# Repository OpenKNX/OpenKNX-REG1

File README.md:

# OpenKNX-REG1

see Wiki: https://github.com/OpenKNX/OpenKNX/wiki/OpenKNX-REG1

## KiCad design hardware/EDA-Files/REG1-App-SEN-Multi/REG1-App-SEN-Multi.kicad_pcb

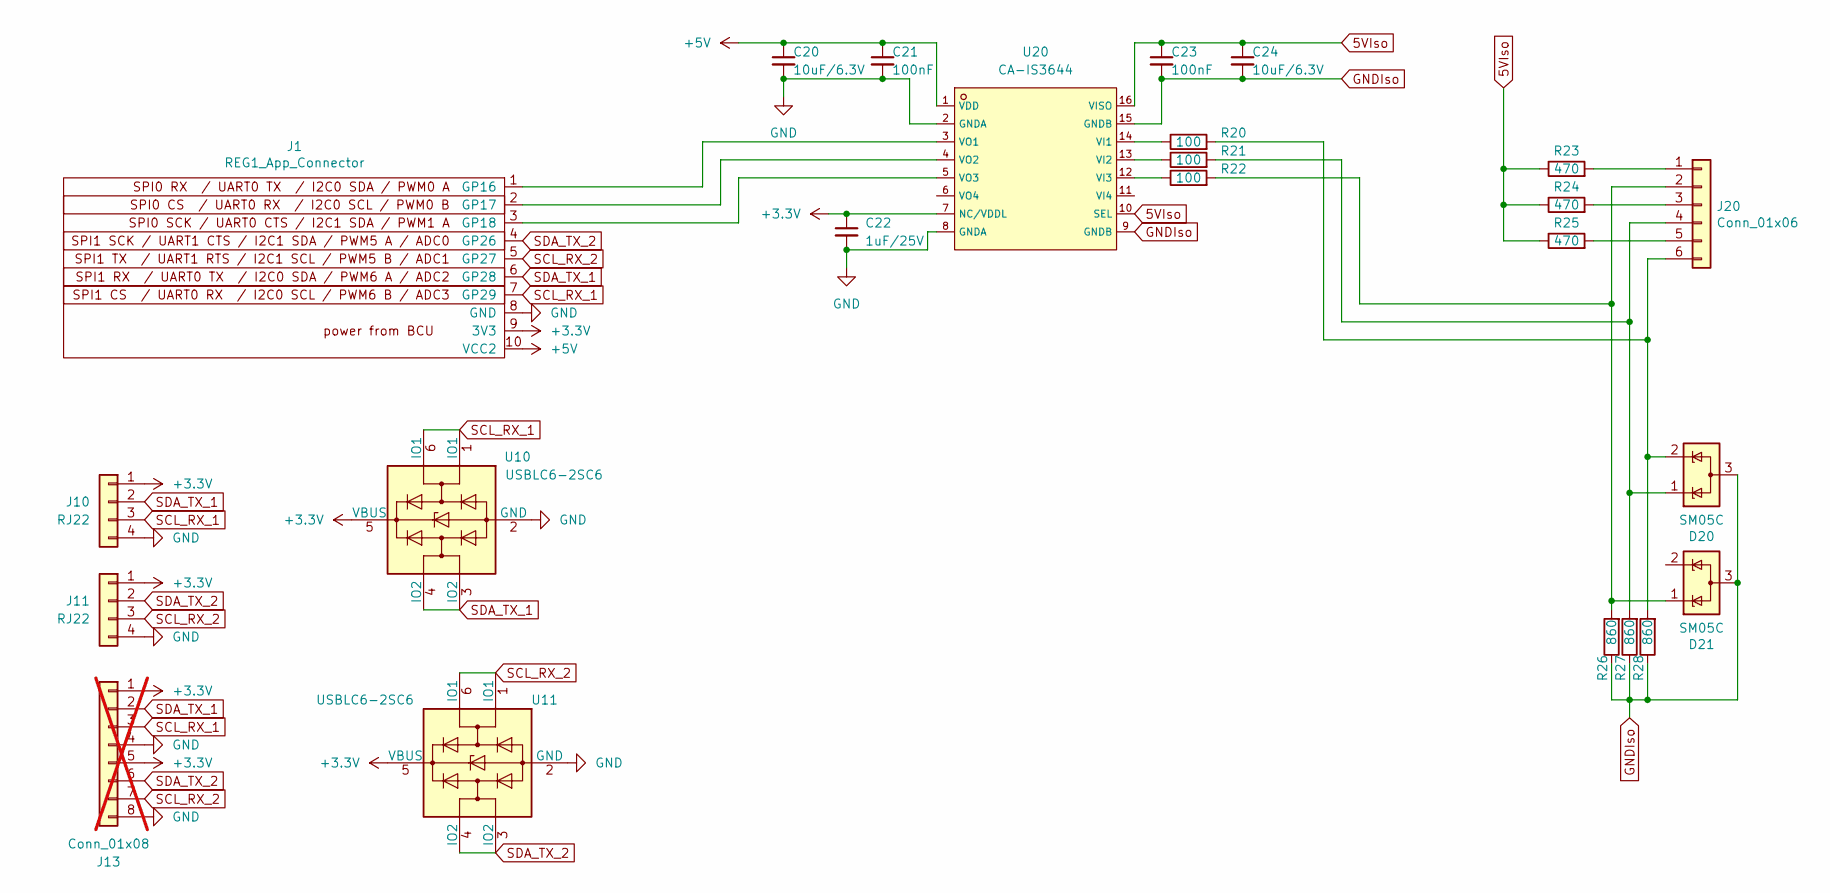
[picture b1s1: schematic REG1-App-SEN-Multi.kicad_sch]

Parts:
C20, C24: 10uF/6.3V; C_0402_1005Metric
C21, C23: 100nF; C_0402_1005Metric
C22: 1uF/25V; C_0402_1005Metric
D20, D21: SM05C; SOT-23
J1: REG1_App_Connector; PinHeader_1x10_P2.54mm_Horizontal
J10, J11: RJ22
J13: Conn_01x08; CONN-TH_8P-P2.54_DIBO_DB2ERC-2.54-8P-GN; not fitted
J20: Conn_01x06; PhoenixContact_MC_1,5_6-G-3.5_1x06_P3.50mm_Horizontal
R20, R21, R22: 100; R_0603_1608Metric
R23, R24, R25: 470; R_0603_1608Metric
R26, R27, R28: 860; R_0603_1608Metric
U10, U11: USBLC6-2SC6; SOT-23-6
U20: CA-IS3644; WSOIC-16_L10.3-W7.5-P1.27-LS10.3-BL

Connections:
5VIso: C23.1, C24.1, R23.1, R24.1, R25.1, U20.10 (SEL), U20.16 (VISO)
+3.3V: C22.1, J1.9 (3V3), J10.1, J11.1, J13.1, J13.5, U10.5 (VBUS), U11.5 (VBUS), U20.7 (NC/VDDL)
+5V: C20.1, C21.1, J1.10 (VCC2), U20.1 (VDD)
GND: C20.2, C21.2, C22.2, J1.8 (GND), J10.4, J11.4, J13.4, J13.8, U10.2 (GND), U11.2 (GND), U20.2 (GNDA), U20.8 (GNDA)
GNDIso: C23.2, C24.2, D20.3 (A), D21.3 (A), R26.1, R27.1, R28.1, U20.9 (GNDB), U20.15 (GNDB)
unnamed: J1.1 (GP16), U20.3 (VO1)
unnamed: J1.2 (GP17), U20.4 (VO2)
unnamed: J1.3 (GP18), U20.5 (VO3)
unnamed: J20.1, R23.2
unnamed: D21.1 (K), J20.2, R22.2, R26.2
unnamed: J20.3, R24.2
unnamed: D20.1 (K), J20.4, R21.2, R27.2
unnamed: J20.5, R25.2
unnamed: D20.2 (K), J20.6, R20.2, R28.2
unnamed: R20.1, U20.14 (VI1)
unnamed: R21.1, U20.13 (VI2)
unnamed: R22.1, U20.12 (VI3)
SCL_RX_1: J1.7 (GP29), J10.3, J13.3, U10.1 (IO1), U10.6 (IO1)
SCL_RX_2: J1.5 (GP27), J11.3, J13.7, U11.1 (IO1), U11.6 (IO1)
SDA_TX_1: J1.6 (GP28), J10.2, J13.2, U10.3 (IO2), U10.4 (IO2)
SDA_TX_2: J1.4 (GP26), J11.2, J13.6, U11.3 (IO2), U11.4 (IO2)

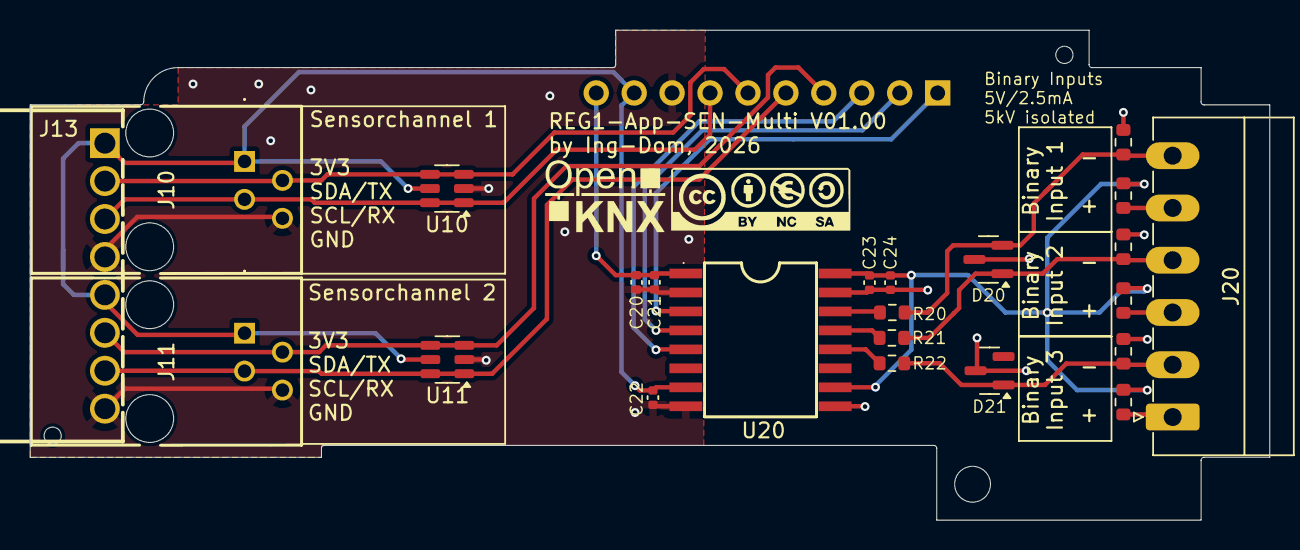
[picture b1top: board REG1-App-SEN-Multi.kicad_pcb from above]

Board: 2 copper layers, 83.0 x 32.8 mm, 24 parts (1 on the bottom side), 21 nets.

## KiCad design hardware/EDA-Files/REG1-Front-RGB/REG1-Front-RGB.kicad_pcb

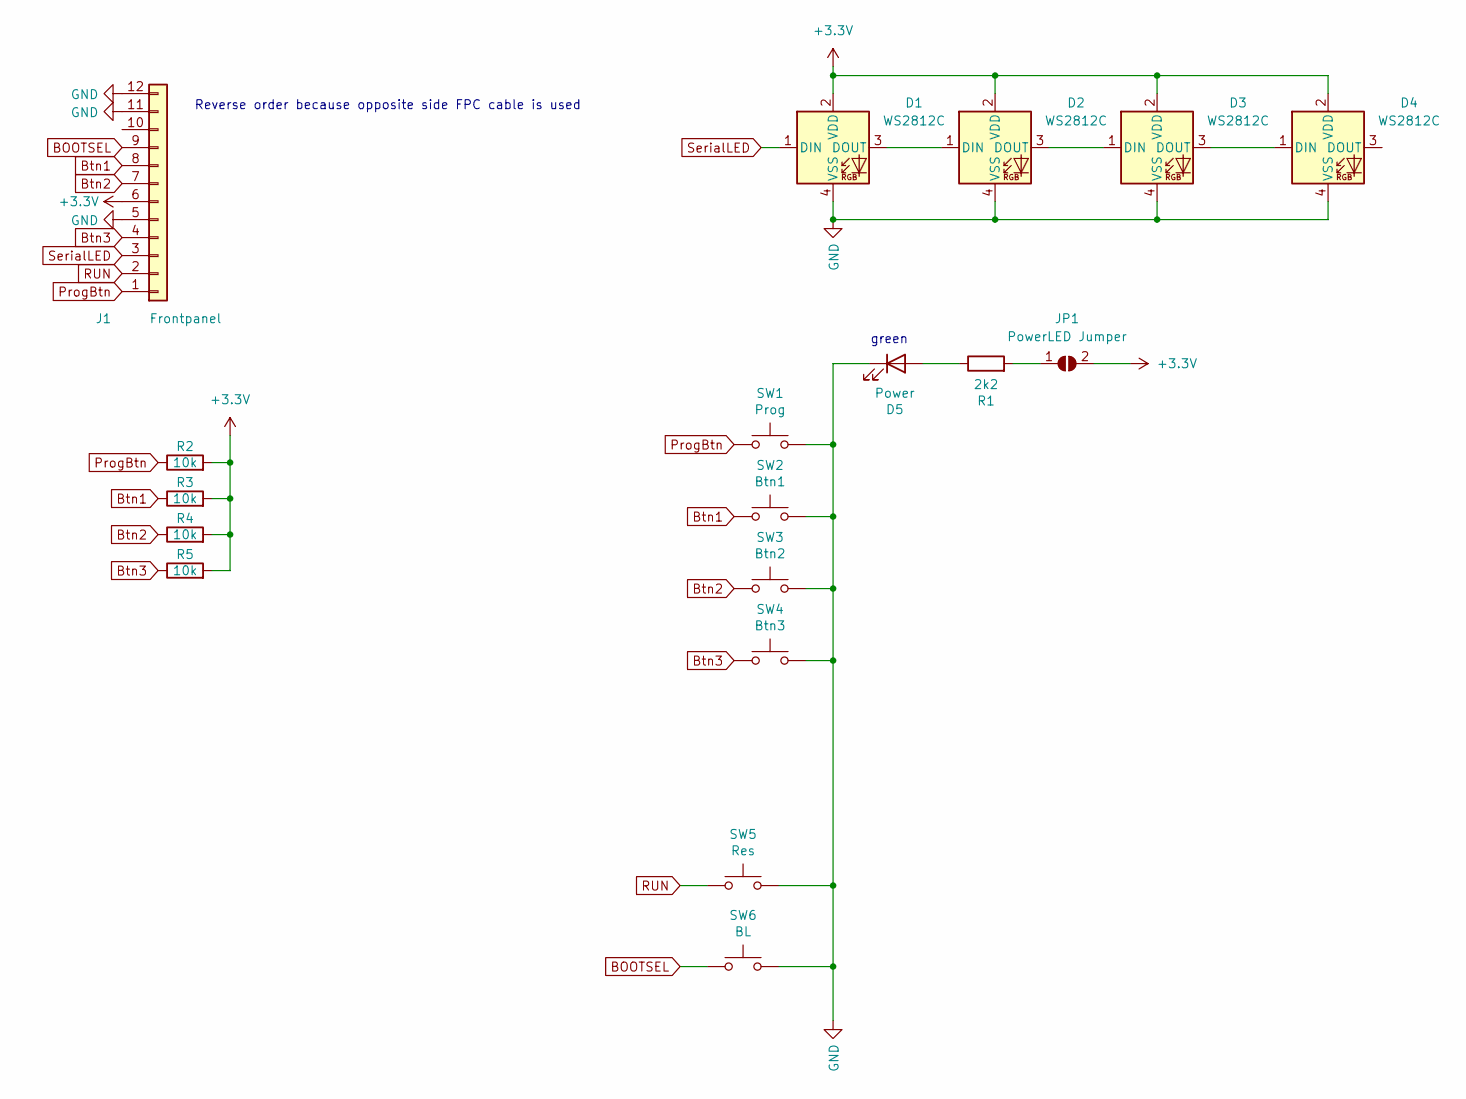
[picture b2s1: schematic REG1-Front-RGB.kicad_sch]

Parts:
D1, D2, D3, D4: WS2812C; LED-SMD_4P-L2.7-W2.4-TL_WS2812C-2427_Handsolder
D5: Power; LED_0603_1608Metric
J1: Frontpanel; C11050_FPC-SMD_P0.5-10P_LSXJ-H2.0-10P
JP1: PowerLED Jumper; SolderJumper-2_P1.3mm_Open_RoundedPad1.0x1.5mm
R1: 2k2; R_0402_1005Metric
R2, R3, R4, R5: 10k; R_0402_1005Metric
SW1: Prog; C455282_SW-SMD_4P-L4.2-W3.3-P2.15-LS5.1
SW2: Btn1; C455282_SW-SMD_4P-L4.2-W3.3-P2.15-LS5.1
SW3: Btn2; C455282_SW-SMD_4P-L4.2-W3.3-P2.15-LS5.1
SW4: Btn3; C455282_SW-SMD_4P-L4.2-W3.3-P2.15-LS5.1
SW5: Res; C455282_SW-SMD_4P-L4.2-W3.3-P2.15-LS5.1
SW6: BL; C455282_SW-SMD_4P-L4.2-W3.3-P2.15-LS5.1

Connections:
+3.3V: D1.2 (VDD), D2.2 (VDD), D3.2 (VDD), D4.2 (VDD), J1.6, JP1.2 (B), R2.2, R3.2, R4.2, R5.2
BOOTSEL: J1.9, SW6.1
Btn1: J1.8, R3.1, SW2.1
Btn2: J1.7, R4.1, SW3.1
Btn3: J1.4, R5.1, SW4.1
GND: D1.4 (VSS), D2.4 (VSS), D3.4 (VSS), D4.4 (VSS), D5.1 (K), J1.5, J1.11, J1.12, SW1.2, SW2.2, SW3.2, SW4.2, SW5.2, SW6.2
unnamed: D1.3 (DOUT), D2.1 (DIN)
unnamed: D2.3 (DOUT), D3.1 (DIN)
unnamed: D3.3 (DOUT), D4.1 (DIN)
unnamed: D5.2 (A), R1.1
unnamed: JP1.1 (A), R1.2
ProgBtn: J1.1, R2.1, SW1.1
RUN: J1.2, SW5.1
SerialLED: D1.1 (DIN), J1.3

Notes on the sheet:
green
Reverse order because opposite side FPC cable is used

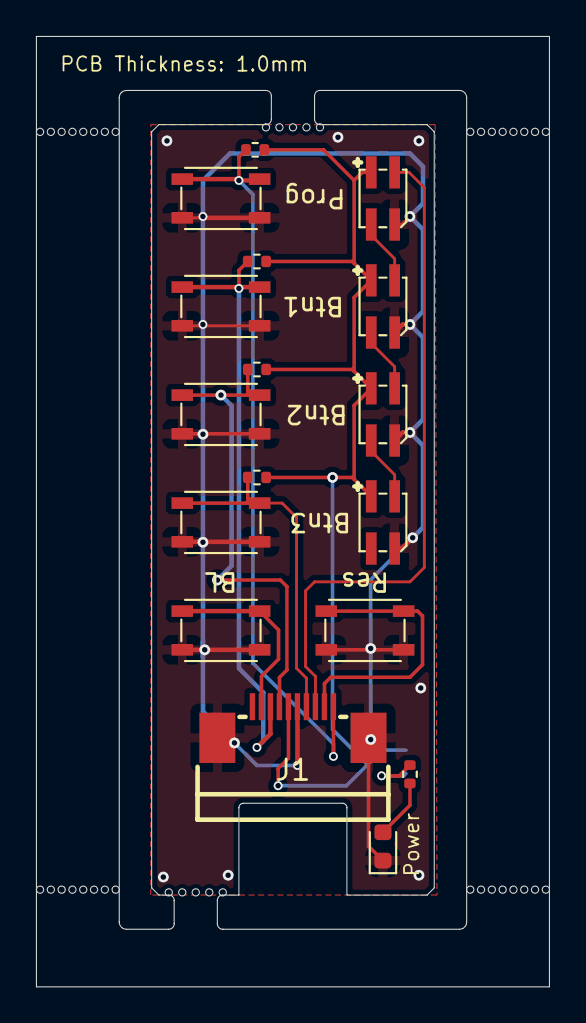
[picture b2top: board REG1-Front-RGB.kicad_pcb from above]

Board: 2 copper layers, 28.5 x 52.8 mm, 24 parts (1 on the bottom side), 14 nets.

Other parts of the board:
e: VAL**; mouse-bite-5.00mm-frame
e#2: VAL**; mouse-bite-5.00mm-frame
mouse-bite: mouse-bite-2.00mm-slot_1side
mouse-bite#2, mouse-bite#3: VAL**; mouse-bite-5.00mm-frame
mouse-bite#4: mouse-bite-2.00mm-slot_1side

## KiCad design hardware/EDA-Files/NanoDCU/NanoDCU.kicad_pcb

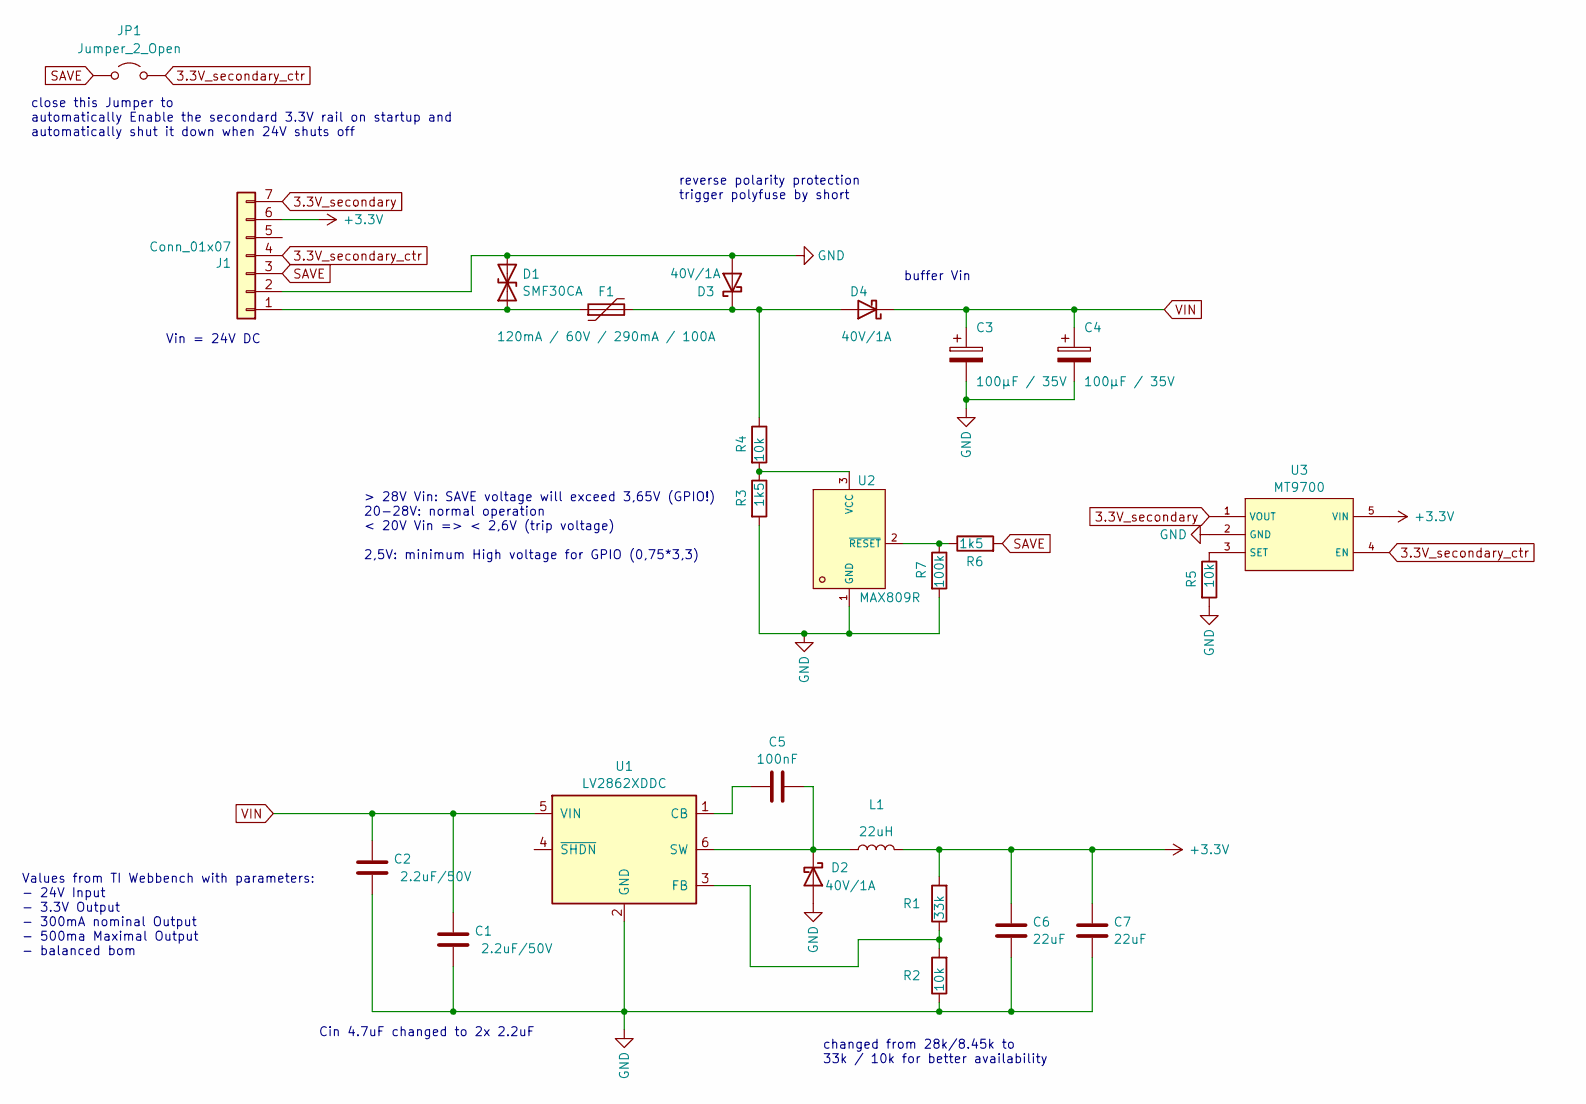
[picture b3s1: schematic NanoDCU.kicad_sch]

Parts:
C1, C2: 2.2uF/50V; C_0805_2012Metric
C3, C4: 100µF / 35V; CP_Elec_6.3x5.8
C5: 100nF; C_0402_1005Metric
C6, C7: 22uF; C_0805_2012Metric
D1: SMF30CA; D_SOD-123F
D2, D3, D4: 40V/1A; D_SOD-123
F1: 120mA / 60V / 290mA / 100A; Fuse_1206_3216Metric
J1: Conn_01x07; PinHeader_1x07_P2.54mm_Vertical
JP1: Jumper_2_Open; SolderJumper-2_P1.3mm_Open_RoundedPad1.0x1.5mm
L1: 22uH; L_Sunlord_SWPA4020
R1: 33k; R_0402_1005Metric
R2, R4, R5: 10k; R_0402_1005Metric
R3, R6: 1k5; R_0402_1005Metric
R7: 100k; R_0402_1005Metric
U1: LV2862XDDC; SOT-23-6
U2: MAX809R; SOT-23
U3: MT9700; SOT-23-5

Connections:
3.3V_secondary: J1.7, U3.1 (VOUT)
3.3V_secondary_ctr: J1.4, JP1.2 (B), U3.4 (EN)
+3.3V: C6.1, C7.1, J1.6, L1.2, R1.2, U3.5 (VIN)
GND: C1.2, C2.2, C3.2, C4.2, C6.2, C7.2, D1.2 (A2), D2.2 (A), D3.2 (A), J1.2, R2.1, R3.2, R5.2, R7.2, U1.2 (GND), U2.1 (GND), U3.2 (GND)
unnamed: D1.1 (A1), F1.1, J1.1
unnamed: C5.2, D2.1 (K), L1.1, U1.6 (SW)
unnamed: D3.1 (K), D4.2 (A), F1.2, R4.1
unnamed: C5.1, U1.1 (CB)
unnamed: R1.1, R2.2, U1.3 (FB)
unnamed: R3.1, R4.2, U2.3 (VCC)
unnamed: R6.1, R7.1, U2.2 (~RESET)
unnamed: R5.1, U3.3 (SET)
SAVE: J1.3, JP1.1 (A), R6.2
VIN: C1.1, C2.1, C3.1, C4.1, D4.1 (K), U1.5 (VIN)

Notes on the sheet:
> 28V Vin: SAVE voltage will exceed 3,65V (GPIO!) 20-28V: normal operation < 20V Vin => < 2,6V (trip voltage) 2,5V: minimum High voltage for GPIO (0,75*3,3)
changed from 28k/8.45k to 33k / 10k for better availability
reverse polarity protection trigger polyfuse by short
close this Jumper to automatically Enable the secondard 3.3V rail on startup and automatically shut it down when 24V shuts off
Cin 4.7uF changed to 2x 2.2uF
Vin = 24V DC
buffer Vin
Values from TI Webbench with parameters: - 24V Input - 3.3V Output - 300mA nominal Output - 500ma Maximal Output - balanced bom

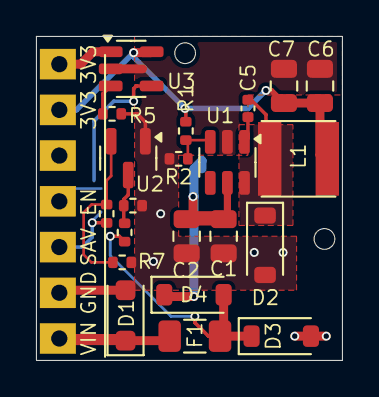
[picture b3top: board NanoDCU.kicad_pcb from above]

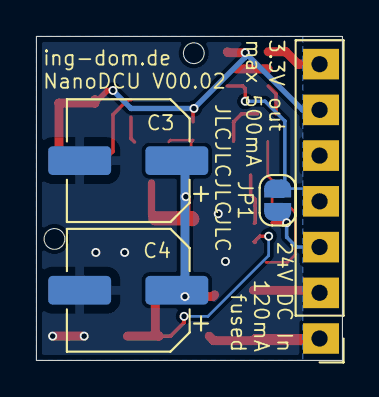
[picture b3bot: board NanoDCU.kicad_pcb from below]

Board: 2 copper layers, 17.0 x 18.0 mm, 25 parts (4 on the bottom side), 14 nets.

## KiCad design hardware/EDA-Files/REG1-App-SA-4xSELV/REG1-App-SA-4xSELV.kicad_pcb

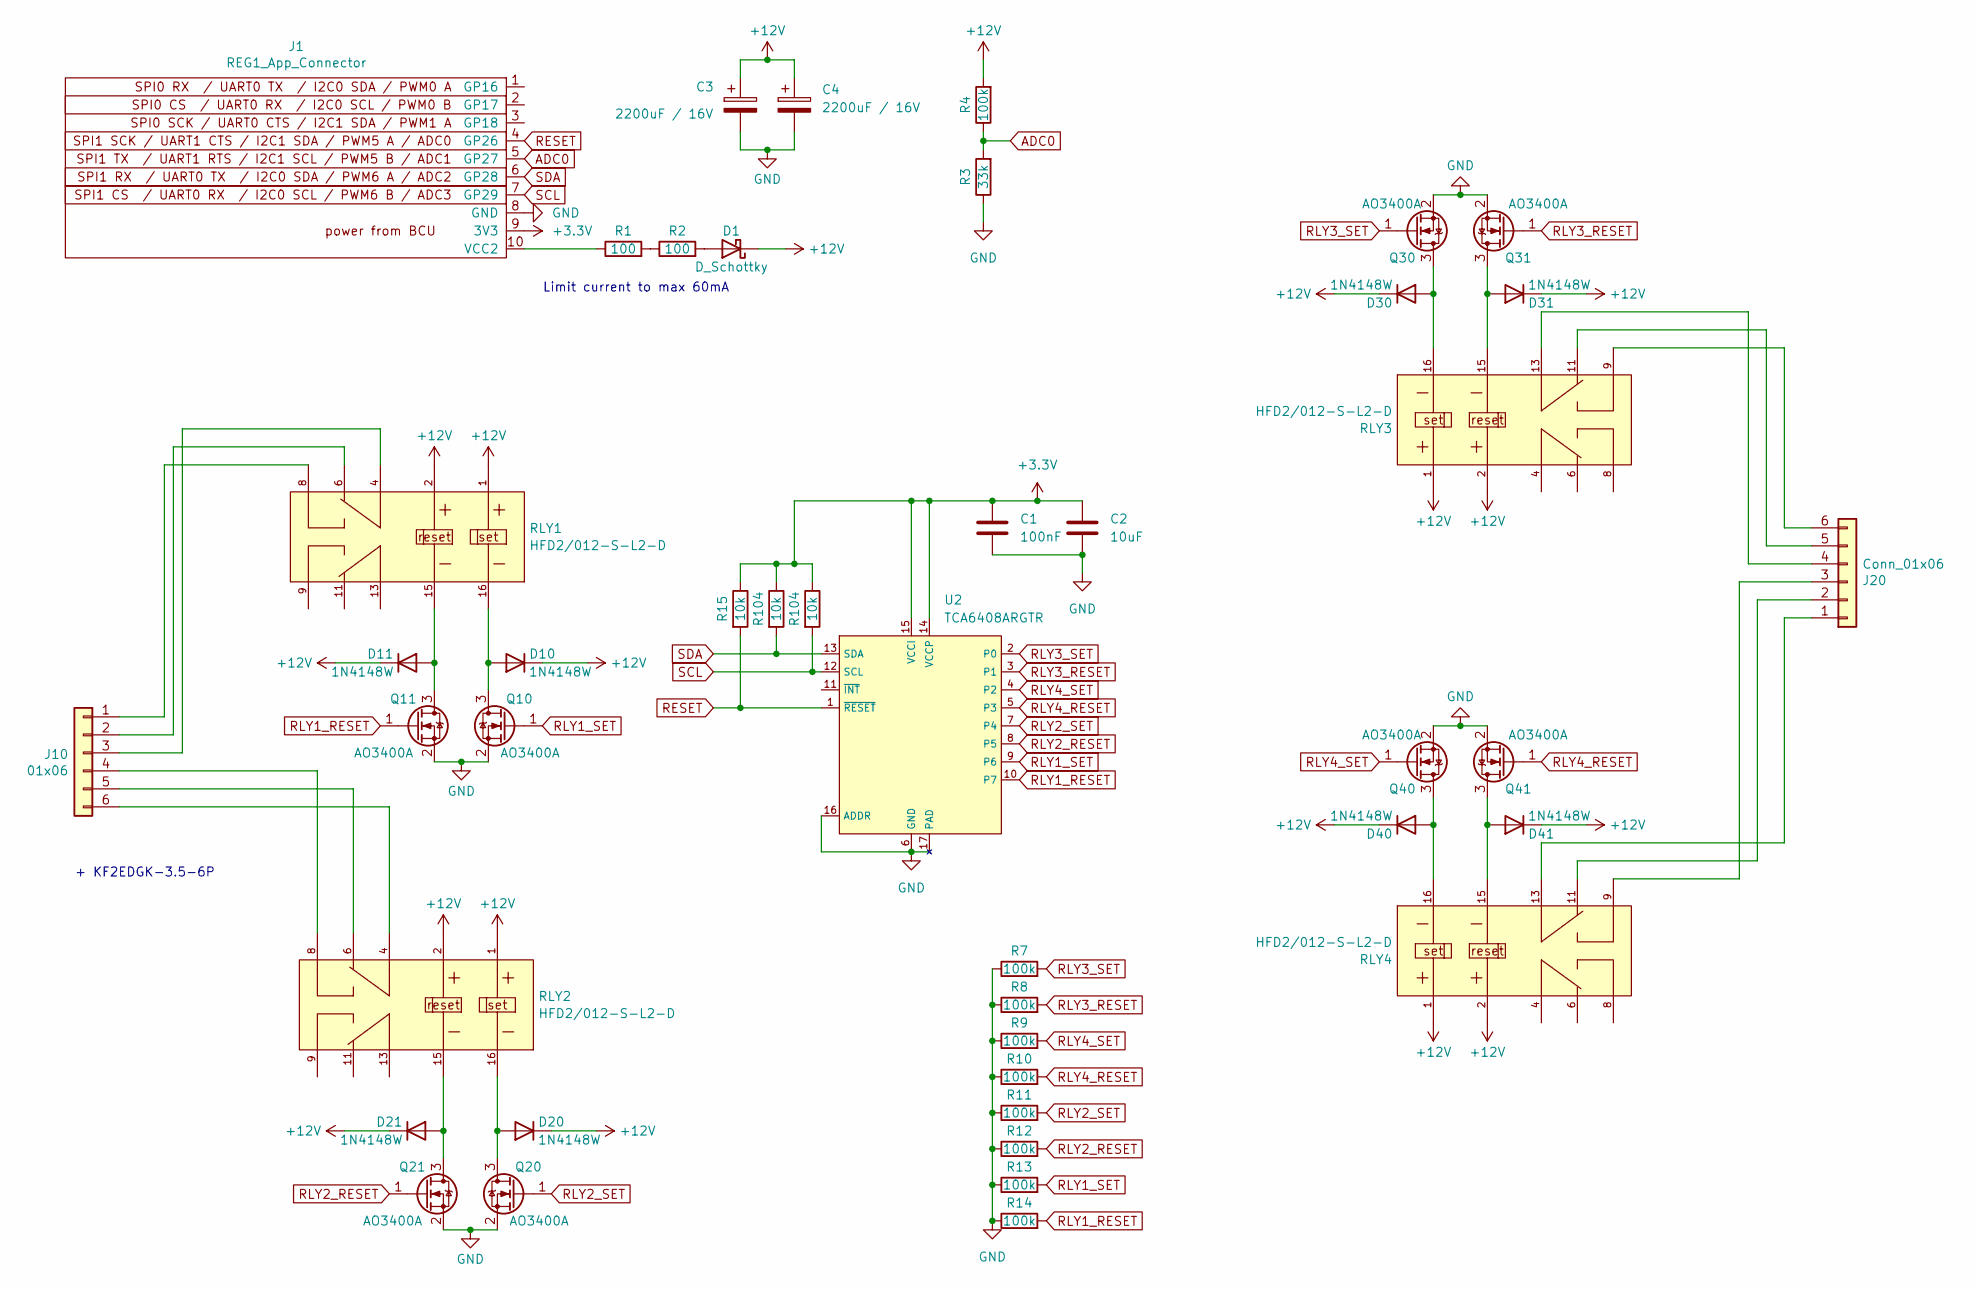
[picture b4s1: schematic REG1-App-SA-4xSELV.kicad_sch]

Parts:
C1: 100nF; R_0402_1005Metric
C2: 10uF; R_0805_2012Metric
C3, C4: 2200uF / 16V; CP_Radial_D10.0mm_H20.0mm_P5.00mm_Horizontal
D1: D_Schottky; D_SOD-323
D10, D11, D20, D21, D30, D31, D40, D41: 1N4148W; D_SOD-323
J1: REG1_App_Connector; PinHeader_1x10_P2.54mm_Horizontal
J10: 01x06; PhoenixContact_MC_1,5_6-G-3.5_1x06_P3.50mm_Horizontal
J20: Conn_01x06; PhoenixContact_MC_1,5_6-G-3.5_1x06_P3.50mm_Horizontal
Q10, Q11, Q20, Q21, Q30, Q31, Q40, Q41: AO3400A; SOT-23
R1, R2: 100; R_1206_3216Metric
R3: 33k; R_0402_1005Metric
R4, R7, R8, R9, R10, R11, R12, R13, R14: 100k; R_0402_1005Metric
R15, R104: 10k; R_0402_1005Metric
RLY1, RLY2, RLY3, RLY4: HFD2/012-S-L2-D; RELAY-TH_HFD2-X-X-L2-X
U2: TCA6408ARGTR; QFN-16-1EP_3x3mm_P0.5mm_EP1.7x1.7mm

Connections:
+3.3V: C1.1, C2.1, J1.9 (3V3), R15.1, U2.14 (VCCP), U2.15 (VCCI); also elsewhere on the board
+12V: C3.1, C4.1, D1.1 (K), D10.1 (K), D11.1 (K), D20.1 (K), D21.1 (K), D30.1 (K), D31.1 (K), D40.1 (K), D41.1 (K), R4.2, RLY1.1, RLY1.2, RLY2.1, RLY2.2, RLY3.1, RLY3.2, RLY4.1, RLY4.2
ADC0: J1.5 (GP27), R3.2, R4.1
GND: C1.2, C2.2, C3.2, C4.2, J1.8 (GND), Q10.2 (S), Q11.2 (S), Q20.2 (S), Q21.2 (S), Q30.2 (S), Q31.2 (S), Q40.2 (S), Q41.2 (S), R3.1, R7.1, R8.1, R9.1, R10.1, R11.1, R12.1, R13.1, R14.1, U2.6 (GND), U2.16 (ADDR), U2.17 (PAD)
unnamed: D1.2 (A), R2.2
unnamed: D10.2 (A), Q10.3 (D), RLY1.16
unnamed: D11.2 (A), Q11.3 (D), RLY1.15
unnamed: D20.2 (A), Q20.3 (D), RLY2.16
unnamed: D21.2 (A), Q21.3 (D), RLY2.15
unnamed: D30.2 (A), Q30.3 (D), RLY3.16
unnamed: D31.2 (A), Q31.3 (D), RLY3.15
unnamed: D40.2 (A), Q40.3 (D), RLY4.16
unnamed: D41.2 (A), Q41.3 (D), RLY4.15
unnamed: J1.10 (VCC2), R1.1
unnamed: J10.1, RLY1.8
unnamed: J10.2, RLY1.6
unnamed: J10.3, RLY1.4
unnamed: J10.4, RLY2.8
unnamed: J10.5, RLY2.6
unnamed: J10.6, RLY2.4
unnamed: J20.1, RLY4.13
unnamed: J20.2, RLY4.11
unnamed: J20.3, RLY4.9
unnamed: J20.4, RLY3.13
unnamed: J20.5, RLY3.11
unnamed: J20.6, RLY3.9
unnamed: R1.2, R2.1
RESET: J1.4 (GP26), R15.2, U2.1 (~RESET)
RLY1_RESET: Q11.1 (G), R14.2, U2.10 (P7)
RLY1_SET: Q10.1 (G), R13.2, U2.9 (P6)
RLY2_RESET: Q21.1 (G), R12.2, U2.8 (P5)
RLY2_SET: Q20.1 (G), R11.2, U2.7 (P4)
RLY3_RESET: Q31.1 (G), R8.2, U2.3 (P1)
RLY3_SET: Q30.1 (G), R7.2, U2.2 (P0)
RLY4_RESET: Q41.1 (G), R10.2, U2.5 (P3)
RLY4_SET: Q40.1 (G), R9.2, U2.4 (P2)
SCL: J1.7 (GP29), U2.12 (SCL); also elsewhere on the board
SDA: J1.6 (GP28), U2.13 (SDA); also elsewhere on the board

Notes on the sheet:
+ KF2EDGK-3.5-6P
Limit current to max 60mA

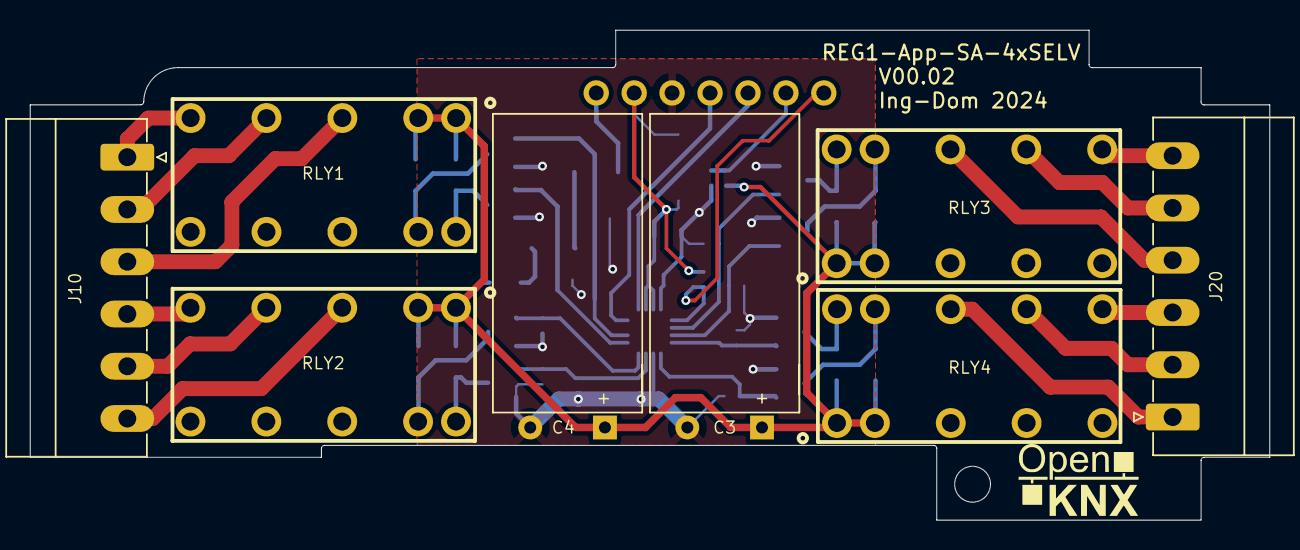
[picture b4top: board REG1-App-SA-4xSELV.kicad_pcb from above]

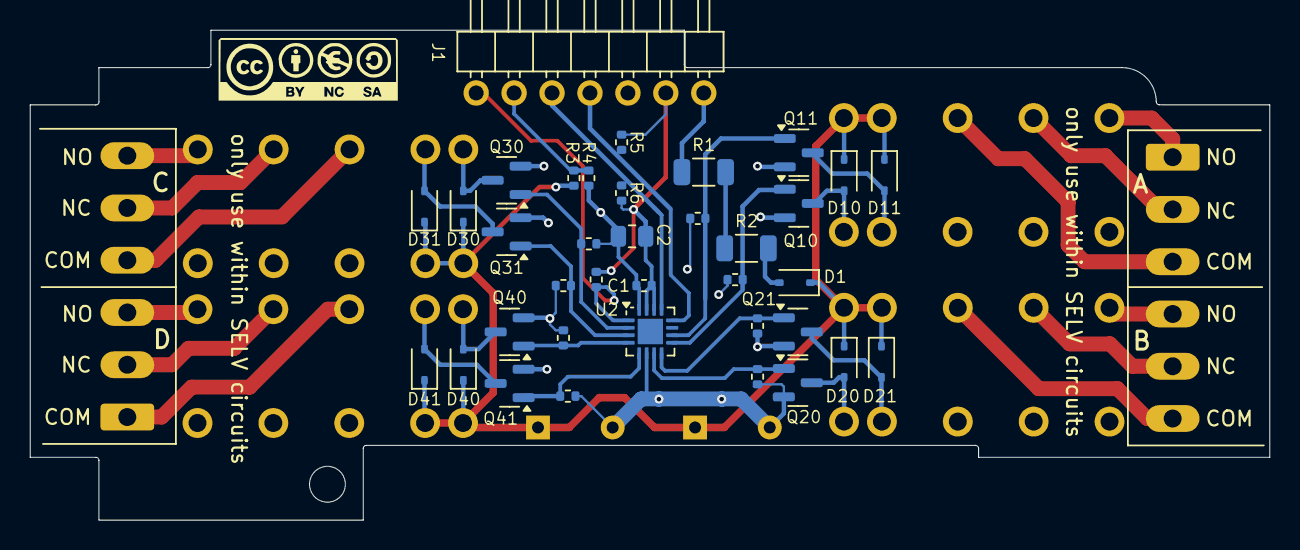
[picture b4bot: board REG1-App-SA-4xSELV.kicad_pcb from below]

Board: 2 copper layers, 83.0 x 32.8 mm, 45 parts (37 on the bottom side), 38 nets.

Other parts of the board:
G1: LOGO; CC-BY-NY-SA_12x4
R5, R6: 10k; R_0402_1005Metric

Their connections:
+3.3V: R5.1, R6.1; also elsewhere on the board
SCL: R5.2; also elsewhere on the board
SDA: R6.2; also elsewhere on the board

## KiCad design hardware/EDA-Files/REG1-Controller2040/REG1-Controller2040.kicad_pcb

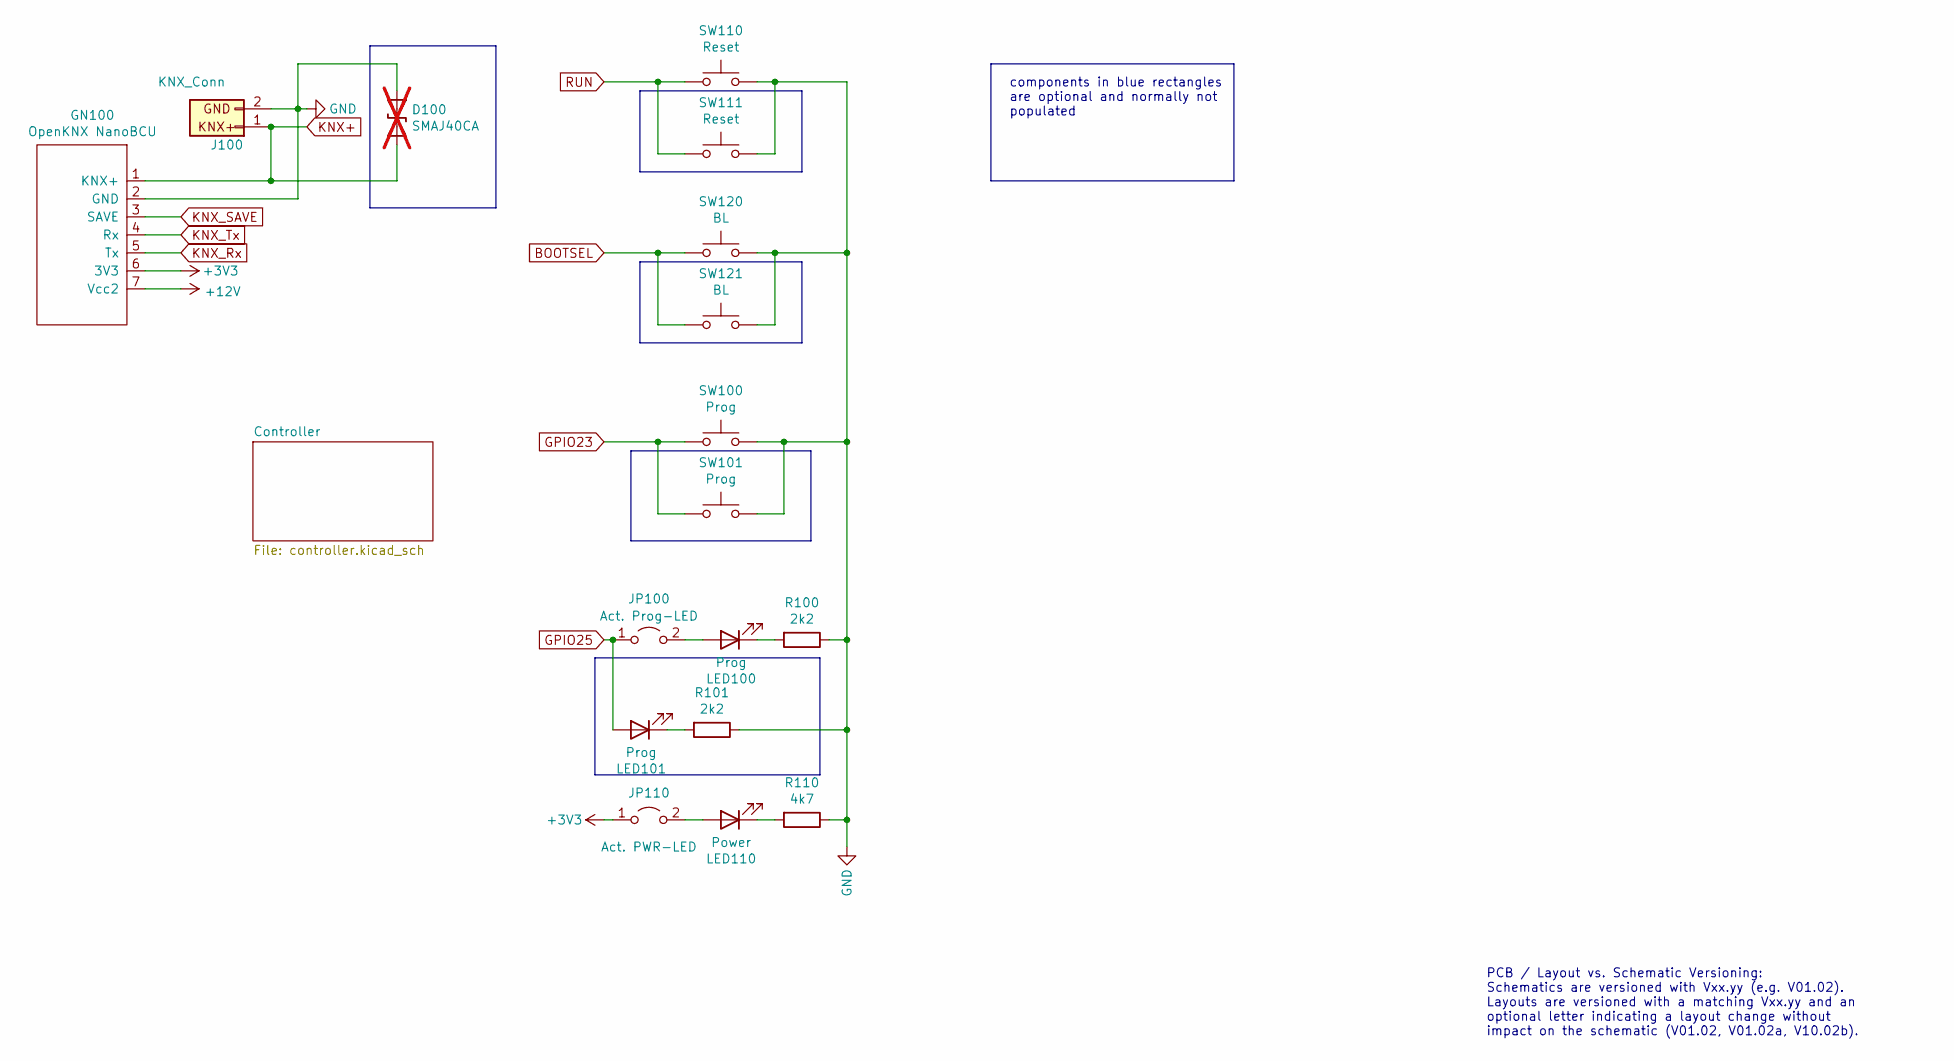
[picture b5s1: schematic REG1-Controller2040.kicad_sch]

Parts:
D100: SMAJ40CA; D_SMA; not fitted
GN100: OpenKNX NanoBCU; NanoBCU2_Vertical_Slot_double
J100: KNX_Conn; KNX_Connector
JP100: Act. Prog-LED; SolderJumper-2_P1.3mm_Open_RoundedPad1.0x1.5mm
JP110: Act. PWR-LED; SolderJumper-2_P1.3mm_Open_RoundedPad1.0x1.5mm
LED100: Prog; D_0603_1608Metric
LED101: Prog; D_0805_2012Metric_Pad1.15x1.40mm_HandSolder
LED110: Power; D_0603_1608Metric
R100: 2k2; R_0402_1005Metric
R101: 2k2; R_0805_2012Metric_Pad1.20x1.40mm_HandSolder
R110: 4k7; R_0402_1005Metric
SW100, SW101: Prog; C455282_SW-SMD_4P-L4.2-W3.3-P2.15-LS5.1_Handsolder
SW110, SW111: Reset; C455282_SW-SMD_4P-L4.2-W3.3-P2.15-LS5.1_Handsolder
SW120, SW121: BL; C455282_SW-SMD_4P-L4.2-W3.3-P2.15-LS5.1_Handsolder

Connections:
+3V3: GN100.6 (3V3), JP110.1 (A); also elsewhere on the board
+12V: GN100.7 (Vcc2); also elsewhere on the board
BOOTSEL: SW120.1, SW121.1; also elsewhere on the board
GND: D100.1 (A1), GN100.2 (GND), J100.2, R100.1, R101.1, R110.1, SW100.2, SW101.2, SW110.2, SW111.2, SW120.2, SW121.2; also elsewhere on the board
GPIO23: SW100.1, SW101.1; also elsewhere on the board
GPIO25: JP100.1 (A), LED101.2 (A); also elsewhere on the board
KNX+: D100.2 (A2), GN100.1 (KNX+), J100.1
KNX_Rx: GN100.5 (Tx); also elsewhere on the board
KNX_SAVE: GN100.3 (SAVE); also elsewhere on the board
KNX_Tx: GN100.4 (Rx); also elsewhere on the board
unnamed: JP100.2 (B), LED100.2 (A)
unnamed: JP110.2 (B), LED110.2 (A)
unnamed: LED100.1 (K), R100.2
unnamed: LED101.1 (K), R101.2
unnamed: LED110.1 (K), R110.2
RUN: SW110.1, SW111.1; also elsewhere on the board

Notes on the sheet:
components in blue rectangles are optional and normally not populated
PCB / Layout vs. Schematic Versioning: Schematics are versioned with Vxx.yy (e.g. V01.02). Layouts are versioned with a matching Vxx.yy and an optional letter indicating a layout change without impact on the schematic (V01.02, V01.02a, V10.02b).

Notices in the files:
hardware/EDA-Files/NanoDCU/NanoDCU.kicad_sch:
CC BY-NC-SA 4.0 https://creativecommons.org/licenses/by-nc-sa/4.0/legalcode.de
hardware/EDA-Files/REG1-App-2xDALI/REG1-App-2xDALI.kicad_sch:
OpenKNX Open Hardware under CC BY-NC-SA 4.0
